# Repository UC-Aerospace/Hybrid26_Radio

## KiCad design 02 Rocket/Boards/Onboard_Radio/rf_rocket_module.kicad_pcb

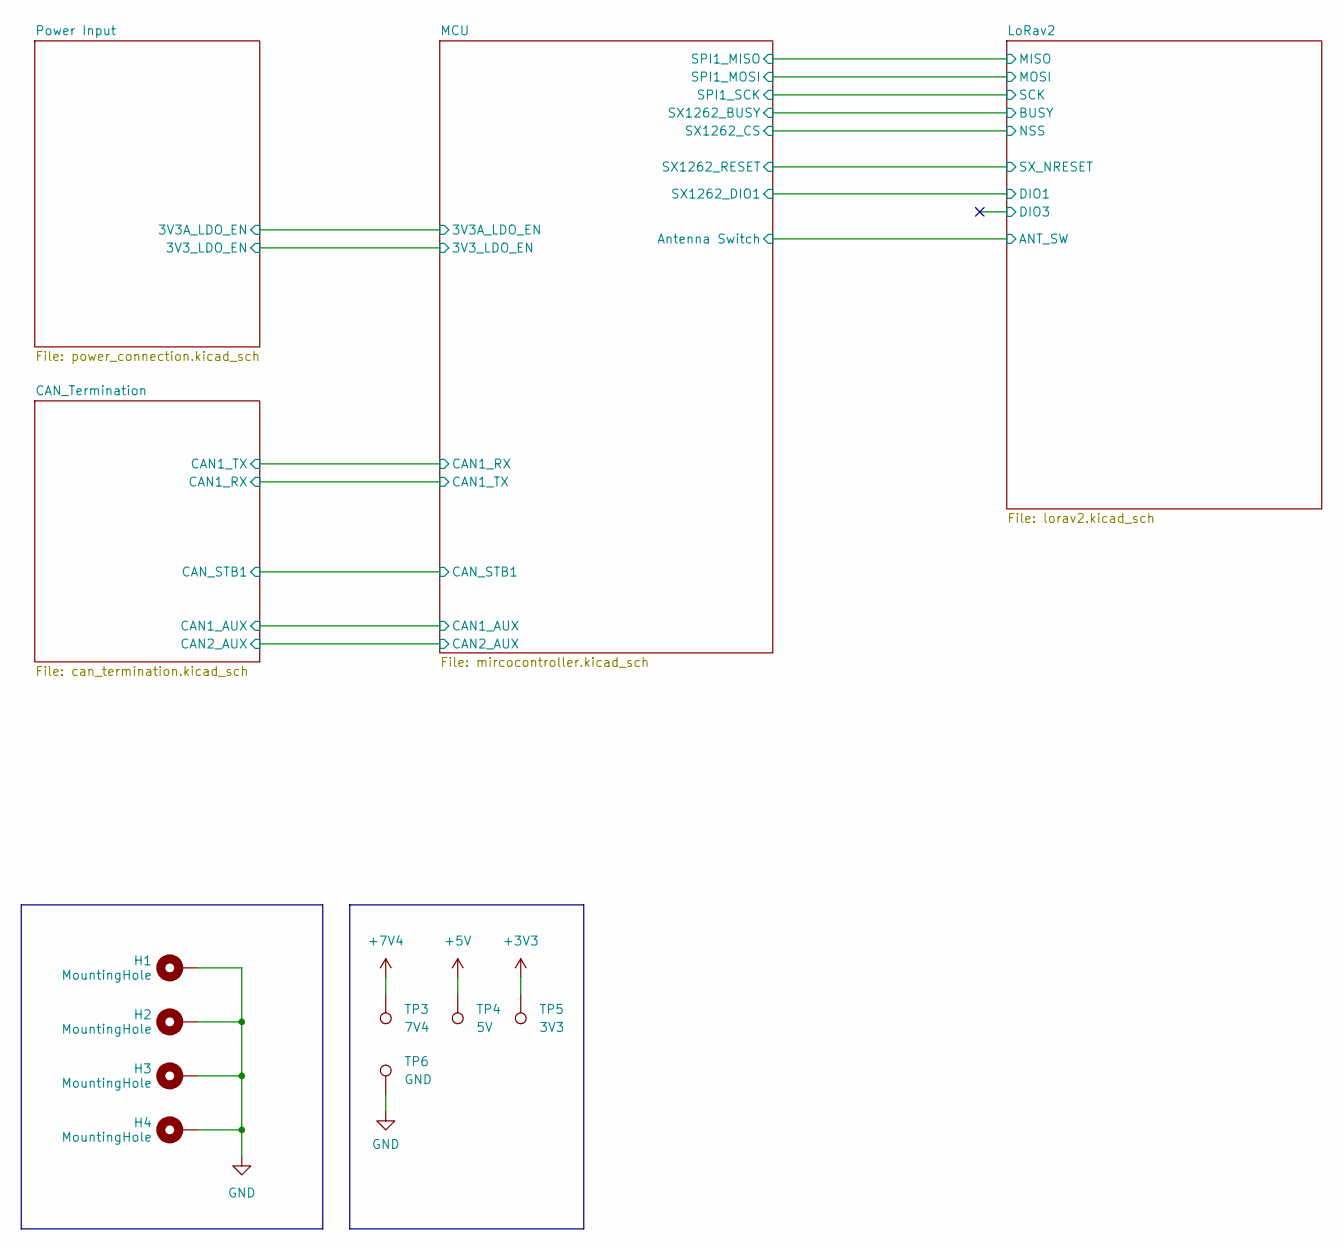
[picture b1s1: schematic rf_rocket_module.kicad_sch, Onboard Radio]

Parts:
H1, H2, H3, H4: MountingHole; MountingHole_3.2mm_M3_DIN965_Pad
TP3: 7V4; TestPoint_Pad_1.0x1.0mm
TP4: 5V; TestPoint_Pad_1.0x1.0mm
TP5: 3V3; TestPoint_Pad_1.0x1.0mm
TP6: GND; TestPoint_Pad_1.0x1.0mm

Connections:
GND: H1.1 (1_1), H2.1 (1_1), H3.1 (1_1), H4.1 (1_1), TP6.1; also elsewhere on the board

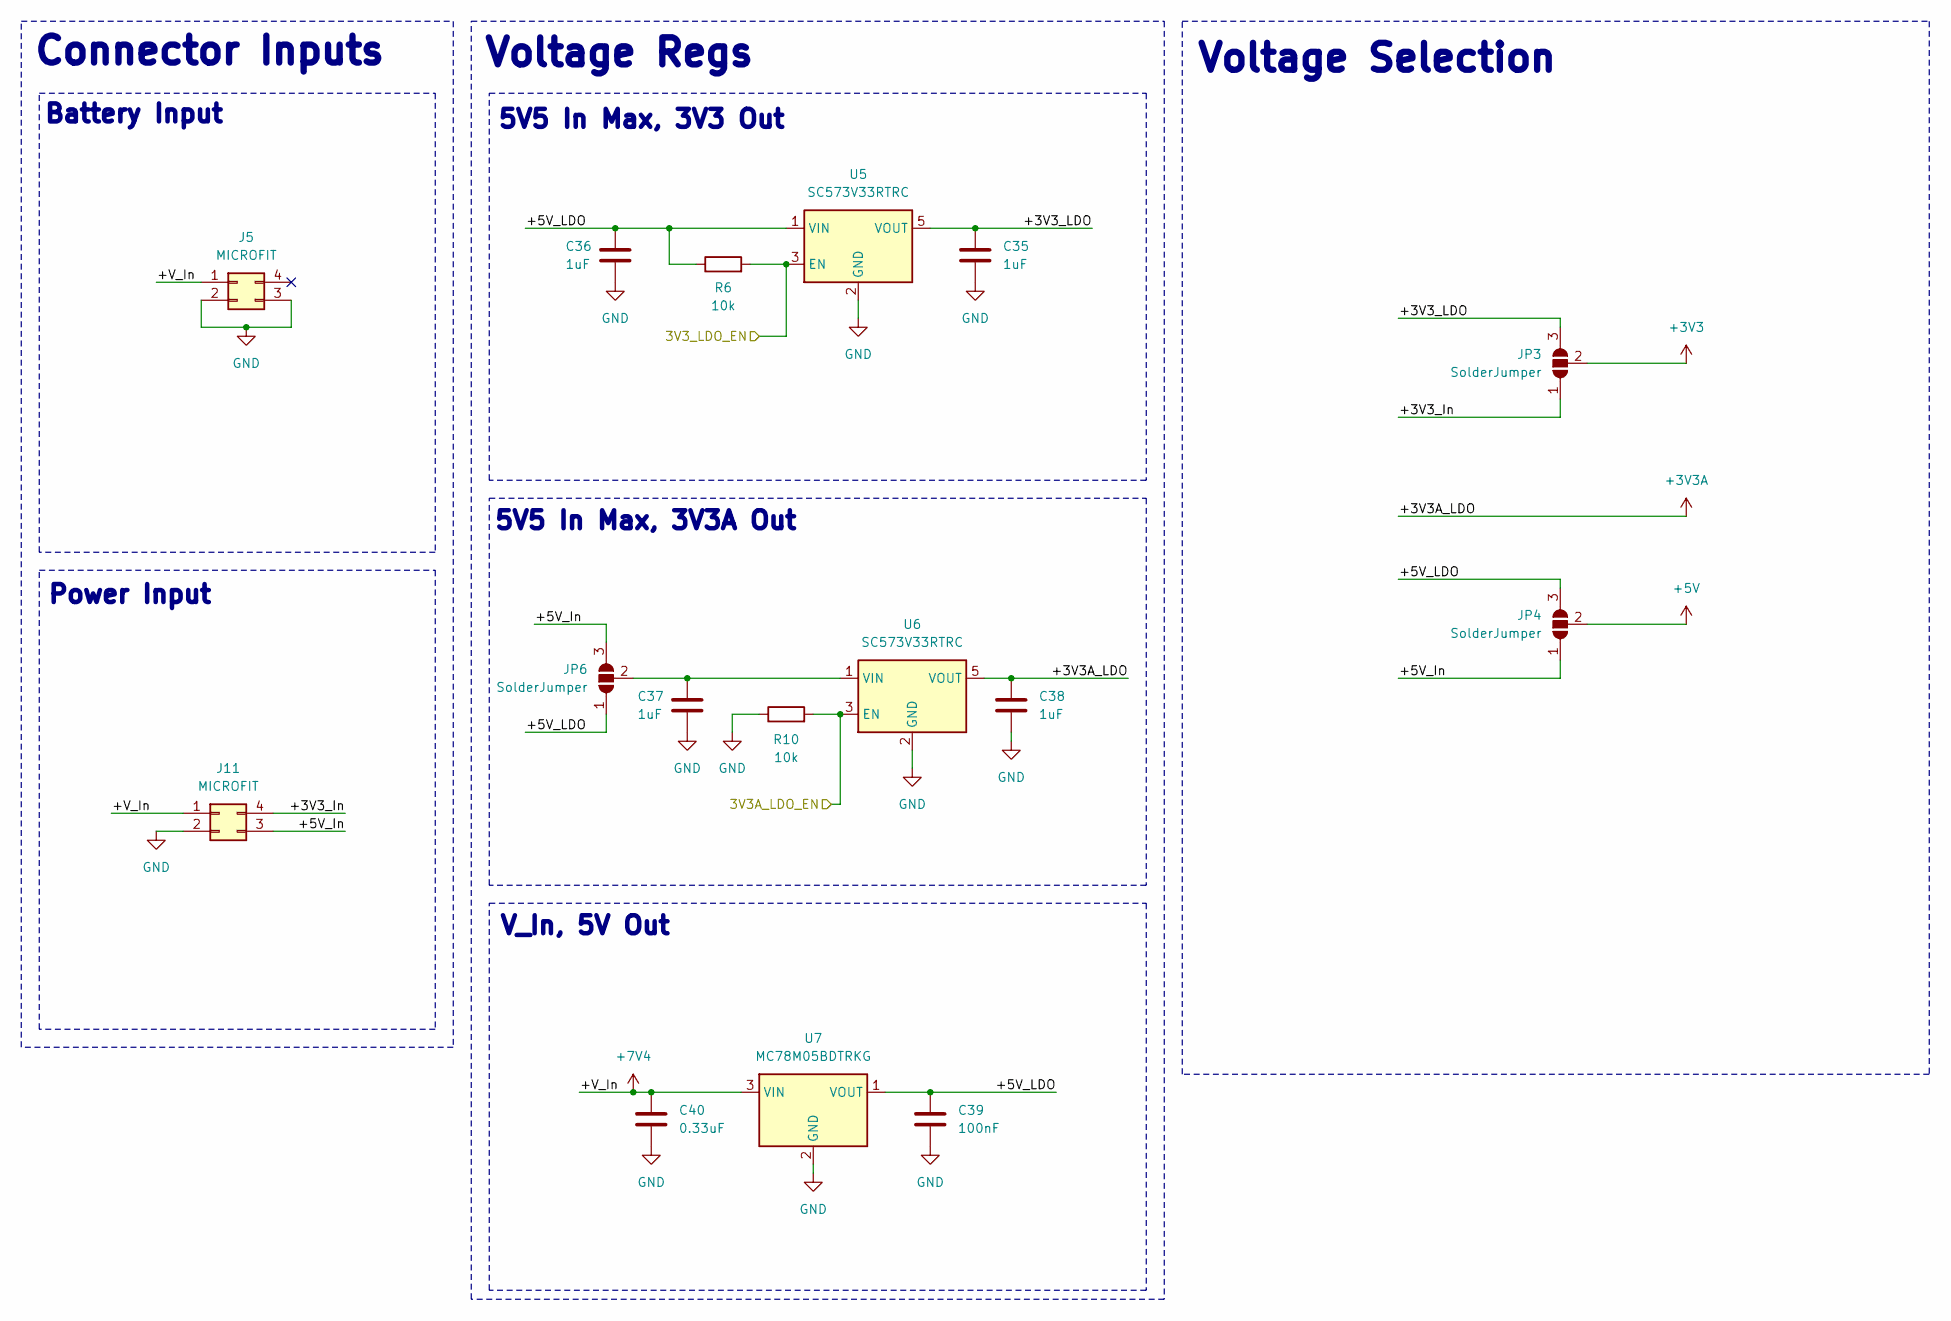
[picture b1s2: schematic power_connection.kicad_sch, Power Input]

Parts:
C35, C36, C37, C38: 1uF; C_0603_1608Metric; Voltage 10V; MPN GCM033C71A104KE02J; LCSC Part # C20041637
C39: 100nF; C_0603_1608Metric; Voltage 100V; MPN CL10E104KC8VPNC; LCSC Part # C16194197
C40: 0.33uF; C_0603_1608Metric; Voltage 50v; MPN CGA3E3X7R1H334K080AB; LCSC Part # C2178511
J5, J11: MICROFIT; Molex_Micro-Fit_3.0_43045-0412_2x02_P3.00mm_Vertical; MPN 0430450412; LCSC Part # C277721
JP3, JP4, JP6: SolderJumper; SolderJumper-3_P1.3mm_Open_RoundedPad1.0x1.5mm
R6, R10: 10k; R_0603_1608Metric; MPN RC0603FR-0710KL; LCSC Part # RC0603FR-0710KL
U5, U6: SC573V33RTRC; SOT-353_SC-70-5; MPN SC573V33RTRC; LCSC Part # C3751903
U7: MC78M05BDTRKG; TO-252-3_TabPin2; MPN MC78M05BDTRKG

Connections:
+3V3: JP3.2 (C); also elsewhere on the board
+3V3A: C38.1, U6.5 (VOUT); also elsewhere on the board
+5V: JP4.2 (C); also elsewhere on the board
+7V4: C40.1, J5.1, J11.1, U7.3 (VIN); also elsewhere on the board
/MCU/3V3A_LDO_EN: R10.2, U6.3 (EN); also elsewhere on the board
/MCU/3V3_LDO_EN: R6.2, U5.3 (EN); also elsewhere on the board
/Power Input/+3V3_In: J11.4, JP3.1 (A)
/Power Input/+3V3_LDO: C35.1, JP3.3 (B), U5.5 (VOUT)
/Power Input/+5V_In: J11.3, JP4.1 (A), JP6.3 (B)
/Power Input/+5V_LDO: C36.1, C39.1, JP4.3 (B), JP6.1 (A), R6.1, U5.1 (VIN), U7.1 (VOUT)
GND: C35.2, C36.2, C37.2, C38.2, C39.2, C40.2, J5.2, J5.3, J11.2, R10.1, U5.2 (GND), U6.2 (GND), U7.2 (GND); also elsewhere on the board
unnamed: C37.1, JP6.2 (C), U6.1 (VIN)

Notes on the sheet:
V_In, 5V Out
Voltage Regs
5V5 In Max, 3V3A Out
5V5 In Max, 3V3 Out
Voltage Selection
Connector Inputs
Power Input
Battery Input

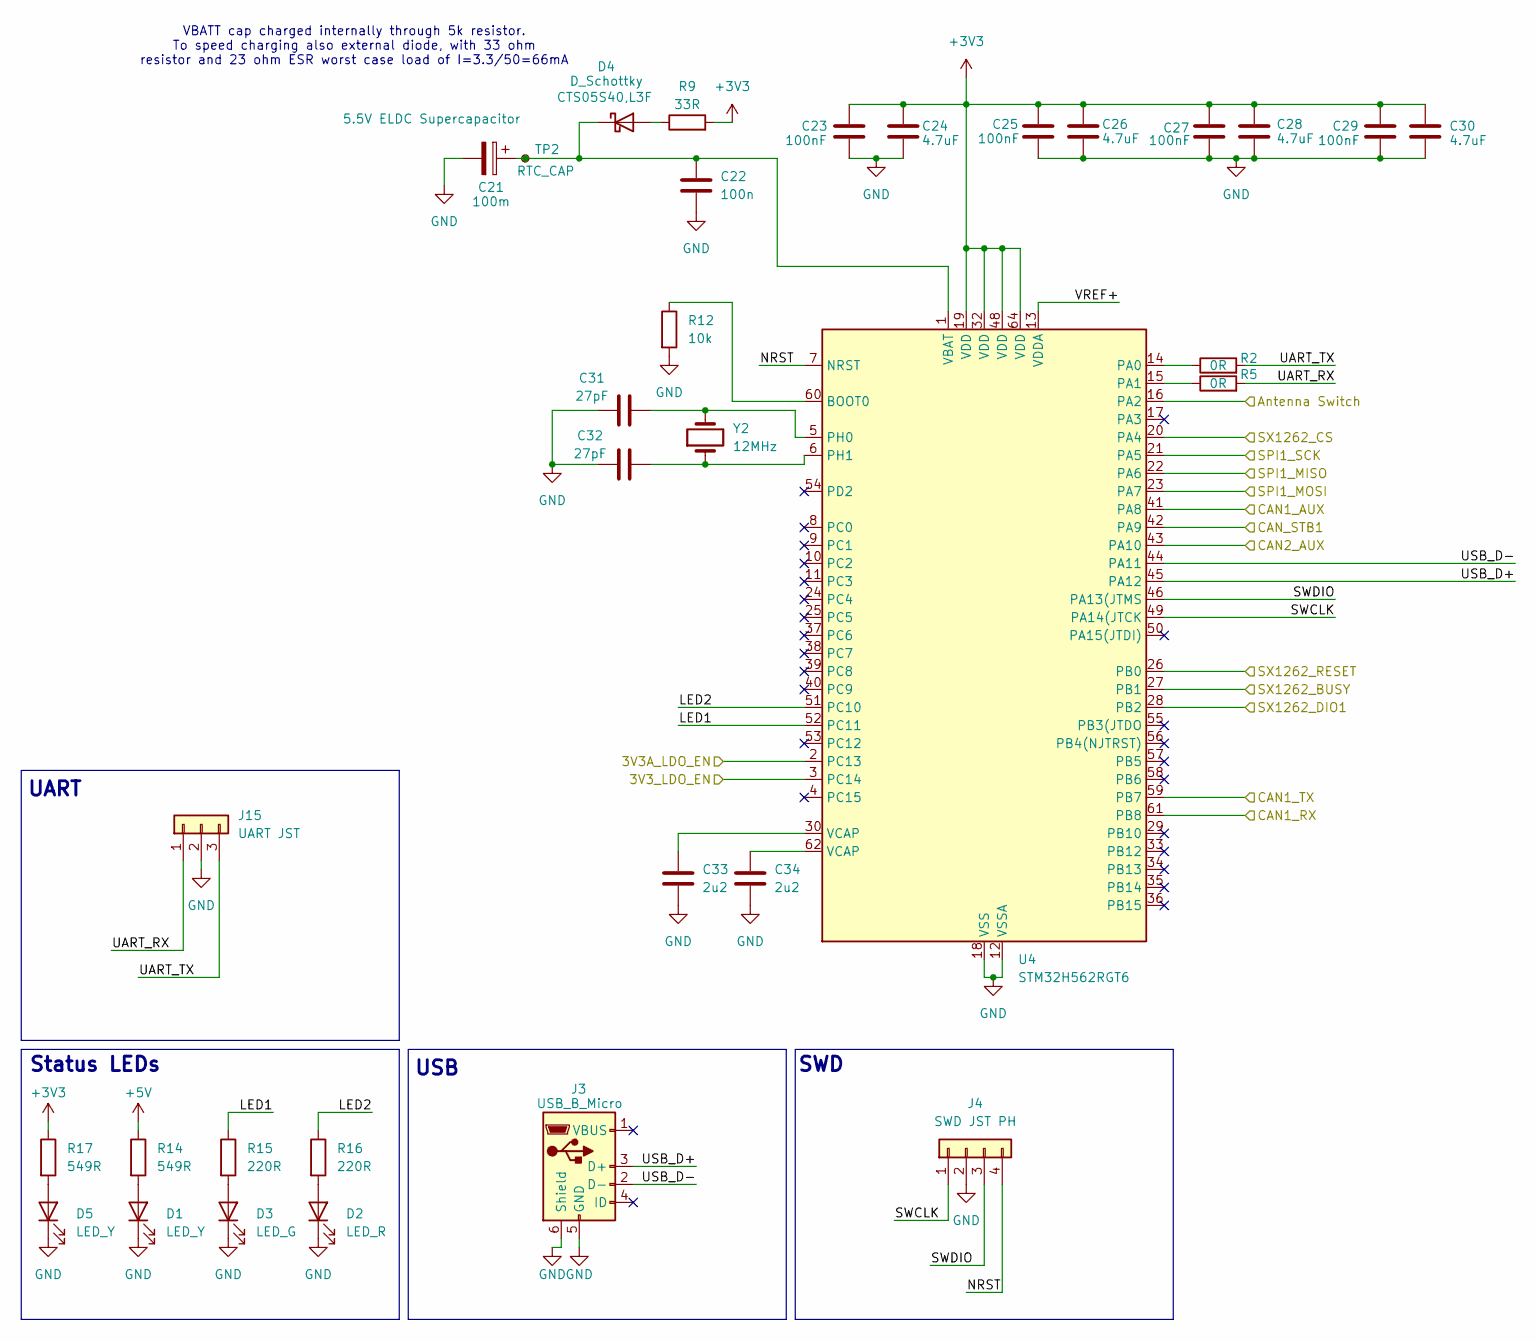
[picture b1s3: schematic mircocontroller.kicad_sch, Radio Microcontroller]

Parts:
C21: 100m; CP_Radial_D14.0mm_P5.00mm; MPN RSCBN1045R5G07014T
C22: 100n; C_0402_1005Metric; Voltage 50V; MPN KAM05FR71H104KH
C23, C25, C27, C29: 100nF; C_0603_1608Metric; Voltage 100V; MPN CL10E104KC8VPNC; LCSC Part # C16194197
C24, C26, C28, C30: 4.7uF; C_0603_1608Metric; Voltage 25V; MPN GRT188C81E475KE13D; LCSC Part # C907917
C31, C32: 27pF; C_0603_1608Metric; MPN GCM1885C2A270JA16D; LCSC Part # C909846
C33, C34: 2u2; R_0603_1608Metric; Voltage 25V; MPN GRM188R61E225KA12D; LCSC Part # C77047
D1, D5: LED_Y; LED_0603_1608Metric; MPN TLMY1100-GS15; LCSC Part # C20433848
D2: LED_R; LED_0603_1608Metric; MPN TLMS1000-GS15; LCSC Part # C23070302
D3: LED_G; LED_0603_1608Metric; MPN TLMG1100-GS15; LCSC Part # C20433785
D4: D_Schottky; D_SOD-882; MPN CTS05S40,L3F; LCSC Part # C396063
J3: USB_B_Micro; USB_Micro-B_Amphenol_10118193-0001LF_Horizontal; Voltage 100V; MPN 10118193-0001LF; LCSC Part # C132562
J4: SWD JST PH; JST_PH_B4B-PH-K_1x04_P2.00mm_Vertical; Voltage 100V; MPN B4B-PH-K-S; LCSC Part # C131334
J15: UART JST; JST_PH_B3B-PH-K_1x03_P2.00mm_Vertical; MPN B3B-PH-K-S
R2, R5: 0R; R_0402_1005Metric; MPN CRCW04020000Z0ED; LCSC Part # C190119
R9: 33R; R_0603_1608Metric; MPN RC0201FR-0733RL; LCSC Part # C295794
R12: 10k; R_0603_1608Metric; MPN RC0603FR-0710KL; LCSC Part # RC0603FR-0710KL
R14, R17: 549R; R_0603_1608Metric; MPN RMCF0603FT549R; LCSC Part # C4237517
R15, R16: 220R; R_0603_1608Metric; MPN RMCF0603JT220R; LCSC Part # C2484076
TP2: RTC_CAP; TestPoint_Pad_1.0x1.0mm
U4: STM32H562RGT6; LQFP-64_10x10mm_P0.5mm; MPN STM32H562RGT6; LCSC Part # C19711662
Y2: 12MHz; Crystal_SMD_Abracon_ABM8G-4Pin_3.2x2.5mm; MPN ABM8G-12.000MHZ-18-D2Y-T

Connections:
+3V3: C23.1, C24.1, C25.1, C26.1, C27.1, C28.1, C29.1, C30.1, R9.2, R17.1, U4.19 (VDD), U4.32 (VDD), U4.48 (VDD), U4.64 (VDD); also elsewhere on the board
+5V: R14.1; also elsewhere on the board
/CAN_Termination/CAN1_AUX: U4.41 (PA8); also elsewhere on the board
/CAN_Termination/CAN1_RX: U4.59 (PB7); also elsewhere on the board
/CAN_Termination/CAN1_TX: U4.61 (PB8); also elsewhere on the board
/CAN_Termination/CAN2_AUX: U4.43 (PA10); also elsewhere on the board
/CAN_Termination/CAN_STB1: U4.42 (PA9); also elsewhere on the board
/LoRav2/ANT_SW: U4.16 (PA2); also elsewhere on the board
/LoRav2/BUSY: U4.27 (PB1); also elsewhere on the board
/LoRav2/DIO1: U4.28 (PB2); also elsewhere on the board
/LoRav2/MISO: U4.22 (PA6); also elsewhere on the board
/LoRav2/MOSI: U4.23 (PA7); also elsewhere on the board
/LoRav2/NSS: U4.20 (PA4); also elsewhere on the board
/LoRav2/SCK: U4.21 (PA5); also elsewhere on the board
/LoRav2/SX_NRESET: U4.26 (PB0); also elsewhere on the board
/MCU/3V3A_LDO_EN: U4.2 (PC13); also elsewhere on the board
/MCU/3V3_LDO_EN: U4.3 (PC14); also elsewhere on the board
/MCU/LED1: R15.1, U4.52 (PC11)
/MCU/LED2: R16.1, U4.51 (PC10)
/MCU/NRST: J4.4, U4.7 (NRST)
/MCU/SWCLK: J4.1, U4.49 (PA14(JTCK)
/MCU/SWDIO: J4.3, U4.46 (PA13(JTMS)
/MCU/UART_RX: J15.1, R5.2
/MCU/UART_TX: J15.3, R2.2
/MCU/USB_D+: J3.3 (D+), U4.45 (PA12)
/MCU/USB_D-: J3.2 (D-), U4.44 (PA11)
/MCU/VREF+: U4.13 (VDDA)
GND: C21.2, C22.2, C23.2, C24.2, C25.2, C26.2, C27.2, C28.2, C29.2, C30.2, C31.1, C32.2, C33.2, C34.2, D1.1 (K), D2.1 (K), D3.1 (K), D5.1 (K), J3.5 (GND), J3.6 (Shield), J4.2, J15.2, R12.2, U4.12 (VSSA), U4.18 (VSS), U4.31 (VSS), U4.47 (VSS), U4.63 (VSS); also elsewhere on the board
unnamed: C33.1, U4.30 (VCAP)
unnamed: C34.1, U4.62 (VCAP)
unnamed: D1.2 (A), R14.2
unnamed: D2.2 (A), R16.2
unnamed: D3.2 (A), R15.2
unnamed: D4.2 (A), R9.1
unnamed: C21.1, C22.1, D4.1 (K), TP2.1, U4.1 (VBAT)
unnamed: D5.2 (A), R17.2
unnamed: R12.1, U4.60 (BOOT0)
unnamed: R2.1, U4.14 (PA0)
unnamed: R5.1, U4.15 (PA1)
unnamed: C31.2, U4.5 (PH0), Y2.3 (2)
unnamed: C32.1, U4.6 (PH1), Y2.1

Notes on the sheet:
VBATT cap charged internally through 5k resistor. To speed charging also external diode, with 33 ohm resistor and 23 ohm ESR worst case load of I=3.3/50=66mA
SWD
UART
USB
Status LEDs

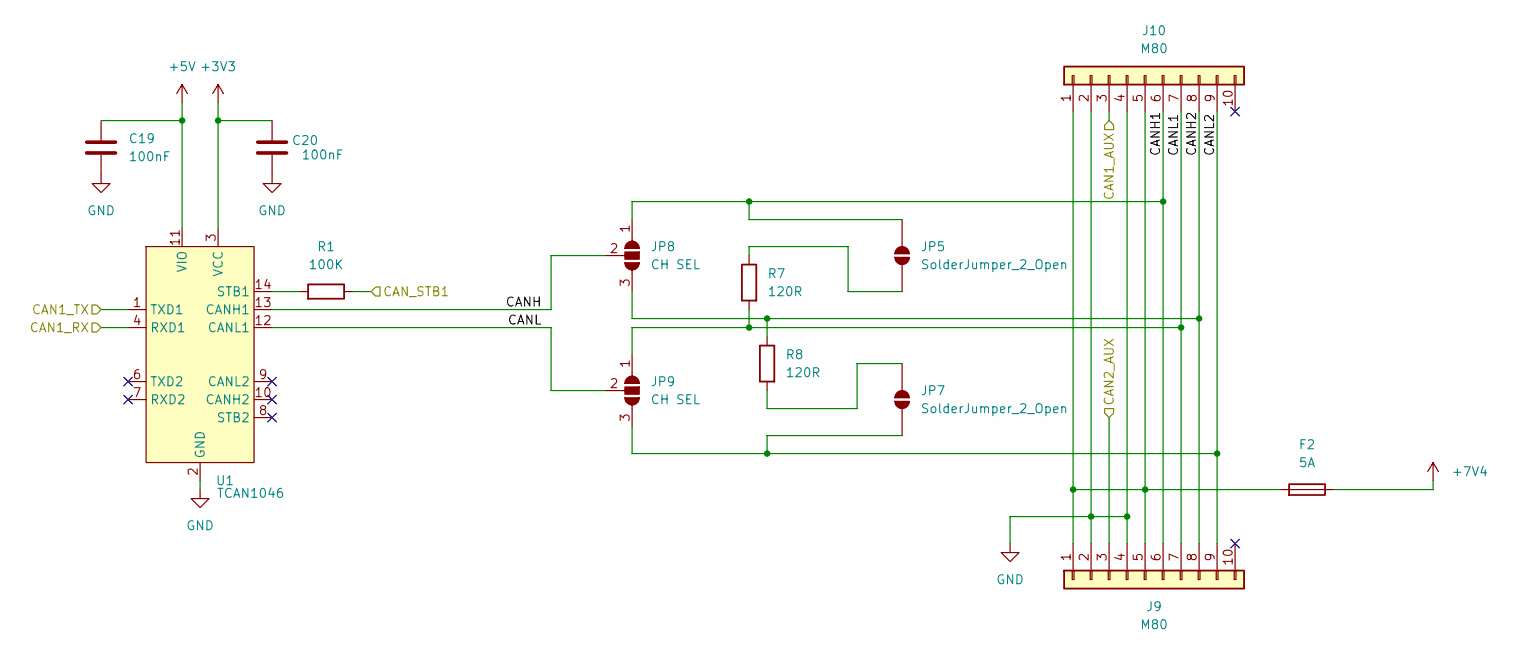
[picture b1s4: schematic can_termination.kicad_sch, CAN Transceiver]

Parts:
C19, C20: 100nF; C_0603_1608Metric; Voltage 100V; MPN CL10E104KC8VPNC; LCSC Part # C16194197
F2: 5A; Fuse_1206_3216Metric; Voltage 63V; MPN C1F 5; LCSC Part # C3166463
J9, J10: M80; HARWIN_M80-5011005; MPN M80-5301042; LCSC Part # C17382082
JP5, JP7: SolderJumper_2_Open; SolderJumper-2_P1.3mm_Open_RoundedPad1.0x1.5mm
JP8, JP9: CH SEL; SolderJumper-3_P1.3mm_Open_RoundedPad1.0x1.5mm
R1: 100K; R_0603_1608Metric; MPN RMCF0603FT100K; LCSC Part # C237792
R7, R8: 120R; R_0603_1608Metric; MPN RMCF0603JT120R; LCSC Part # C3995226
U1: TCAN1046; Texas_DYY0014A_TSOT-23-14; MPN TCAN1046AVDYYRQ1; LCSC Part # C3233845

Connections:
+3V3: C20.1, U1.3 (VCC); also elsewhere on the board
+5V: C19.1, U1.11 (VIO); also elsewhere on the board
+7V4: F2.1; also elsewhere on the board
/CAN_Termination/CAN1_AUX: J10.3; also elsewhere on the board
/CAN_Termination/CAN1_RX: U1.4 (RXD1); also elsewhere on the board
/CAN_Termination/CAN1_TX: U1.1 (TXD1); also elsewhere on the board
/CAN_Termination/CAN2_AUX: J9.3; also elsewhere on the board
/CAN_Termination/CANH: JP8.2 (C), U1.13 (CANH1)
/CAN_Termination/CANH1: J9.6, J10.6, JP5.2 (B), JP8.1 (A)
/CAN_Termination/CANH2: J9.8, J10.8, JP8.3 (B), R8.1
/CAN_Termination/CANL: JP9.2 (C), U1.12 (CANL1)
/CAN_Termination/CANL1: J9.7, J10.7, JP9.1 (A), R7.2
/CAN_Termination/CANL2: J9.9, J10.9, JP7.1 (A), JP9.3 (B)
/CAN_Termination/CAN_STB1: R1.1; also elsewhere on the board
GND: C19.2, C20.2, J9.2, J9.4, J10.2, J10.4, U1.2 (GND), U1.5 (GND); also elsewhere on the board
unnamed: F2.2, J9.1, J9.5, J10.1, J10.5
unnamed: JP5.1 (A), R7.1
unnamed: JP7.2 (B), R8.2
unnamed: R1.2, U1.14 (STB1)

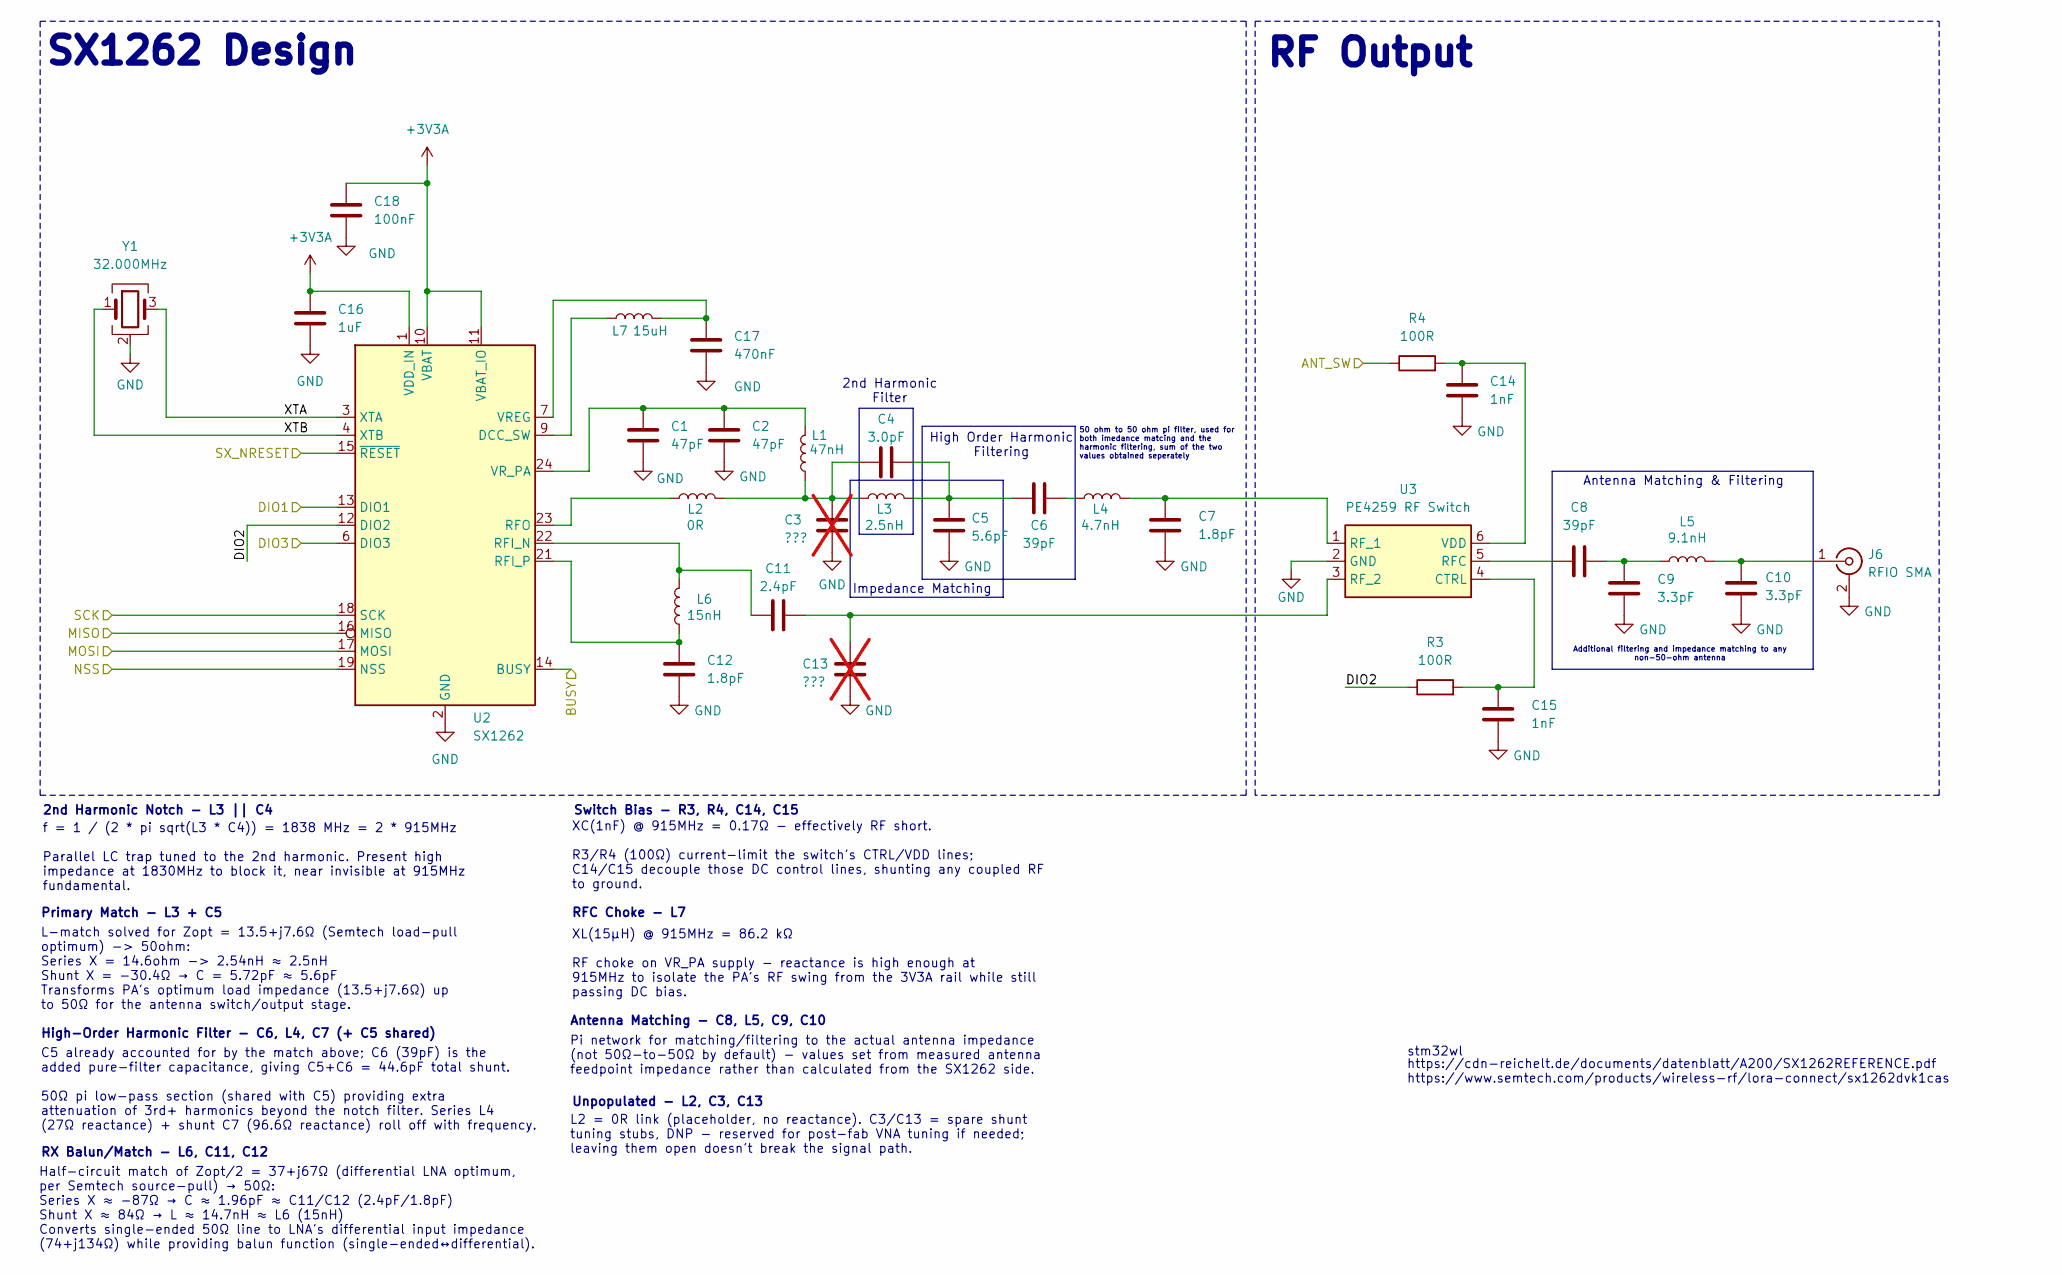
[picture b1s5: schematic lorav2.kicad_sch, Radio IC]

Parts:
C1, C2: 47pF; C_0402_1005Metric; Voltage 50V; MPN GJM1555C1H470JB01D; LCSC Part # C161322
C3, C13: ???; C_0402_1005Metric; not fitted
C4: 3.0pF; C_0402_1005Metric; Voltage 50V; MPN GJM1555C1H3R0BB01D; LCSC Part # C88891
C5: 5.6pF; C_0402_1005Metric; Voltage 50V; MPN GJM1555C1H5R6CB01D; LCSC Part # C88895
C6, C8: 39pF; C_0402_1005Metric; Voltage 50V; MPN GJM1555C1H390JB01D; LCSC Part # C426038
C7, C12: 1.8pF; C_0402_1005Metric; Voltage 50V; MPN GJM1555C1H1R8BB01D; LCSC Part # C76902
C9, C10: 3.3pF; C_0402_1005Metric; Voltage 50V; MPN GJM1555C1H3R3BB01D; LCSC Part # C76906
C11: 2.4pF; C_0402_1005Metric; Voltage 50V; MPN GJM1555C1H2R4BB01D; LCSC Part # C88888
C14, C15: 1nF; C_0402_1005Metric; Voltage 100V; MPN GRM155R72A102KA01D; LCSC Part # C162197
C16: 1uF; C_0402_1005Metric; Voltage 16V; MPN GRM155R61C105KA12D; LCSC Part # C77006
C17: 470nF; C_0402_1005Metric; Voltage 10V; MPN GRM155R71A474KE01D; LCSC Part # C88946
C18: 100nF; C_0402_1005Metric; Voltage 50V; MPN GRM155R71H104KE14D; LCSC Part # C77020
J6: RFIO SMA; SMA-KE-16.5A_EdgeMount; MPN 142-0701-841; LCSC Part # C3173357
L1: 47nH; L_0402_1005Metric; MPN LQW15AN47NJ00D; LCSC Part # C192855
L2: 0R; R_0402_1005Metric; MPN CRCW04020000Z0ED; LCSC Part # C190119
L3: 2.5nH; L_0402_1005Metric; MPN LQW15AN2N5C00D; LCSC Part # C703121
L4: 4.7nH; L_0402_1005Metric; MPN LQW15AN4N7C00D; LCSC Part # C167480
L5: 9.1nH; L_0402_1005Metric; MPN LQW15AN9N1H00D; LCSC Part # C337956
L6: 15nH; L_0402_1005Metric; MPN LQW15AN15NH00D; LCSC Part # C91621
L7: 15uH; L_0805_2012Metric; MPN MLZ2012M150WT000; LCSC Part # C383402
R3, R4: 100R; R_0402_1005Metric; MPN CRCW0402100RFKED; LCSC Part # C82865
U2: SX1262; QFN-24-1EP_4x4mm_P0.5mm_EP2.6x2.6mm; MPN SX1262IMLTRT; LCSC Part # C191341
U3: PE4259 RF Switch; SOT-363_SC-70-6; MPN 4259-63; LCSC Part # C470892
Y1: 32.000MHz; Oscillator_SMD_ECS_2520MV-xxx-xx-4Pin_2.5x2.0mm; MPN TYETBCSANF-32.000000

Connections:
+3V3A: C16.1, C18.1, U2.1 (VDD_IN), U2.10 (VBAT), U2.11 (VBAT_IO); also elsewhere on the board
/LoRav2/ANT_SW: R4.1; also elsewhere on the board
/LoRav2/BUSY: U2.14 (BUSY); also elsewhere on the board
/LoRav2/DIO1: U2.13 (DIO1); also elsewhere on the board
/LoRav2/DIO2: R3.1, U2.12 (DIO2)
/LoRav2/DIO3: U2.6 (DIO3)
/LoRav2/MISO: U2.16 (MISO); also elsewhere on the board
/LoRav2/MOSI: U2.17 (MOSI); also elsewhere on the board
/LoRav2/NSS: U2.19 (NSS); also elsewhere on the board
/LoRav2/SCK: U2.18 (SCK); also elsewhere on the board
/LoRav2/SX_NRESET: U2.15 (~RESET); also elsewhere on the board
/LoRav2/XTA: U2.3 (XTA), Y1.3
/LoRav2/XTB: U2.4 (XTB), Y1.1
GND: C1.2, C2.2, C3.2, C5.2, C7.2, C9.2, C10.2, C12.2, C13.2, C14.2, C15.2, C16.2, C17.2, C18.2, J6.2 (Ext), U2.2 (GND), U2.5 (GND), U2.8 (GND), U2.20 (GND), U2.25 (GND), U3.2 (GND), Y1.2 (G), Y1.4 (G); also elsewhere on the board
unnamed: C3.1, C4.1, L1.1, L2.2, L3.1
unnamed: C4.2, C5.1, C6.1, L3.2
unnamed: C6.2, L4.1
unnamed: C8.2, C9.1, L5.1
unnamed: C10.1, J6.1 (In), L5.2
unnamed: L7.1, U2.9 (DCC_SW)
unnamed: C11.1, L6.2, U2.22 (RFI_N)
unnamed: C12.1, L6.1, U2.21 (RFI_P)
unnamed: L2.1, U2.23 (RFO)
unnamed: C17.1, L7.2, U2.7 (VREG)
unnamed: C1.1, C2.1, L1.2, U2.24 (VR_PA)
unnamed: C15.1, R3.2, U3.4 (CTRL)
unnamed: C8.1, U3.5 (RFC)
unnamed: C7.1, L4.2, U3.1 (RF_1)
unnamed: C11.2, C13.1, U3.3 (RF_2)
unnamed: C14.1, R4.2, U3.6 (VDD)

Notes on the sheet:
Additional filtering and impedance matching to any non-50-ohm antenna
C5 already accounted for by the match above; C6 (39pF) is the added pure-filter capacitance, giving C5+C6 = 44.6pF total shunt. 50Ω pi low-pass section (shared with C5) providing extra attenuation of 3rd+ harmonics beyond the notch filter. Series L4 (27Ω reactance) + shunt C7 (96.6Ω reactance) roll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
https://cdn-reichelt.de/documents/datenblatt/A200/SX1262REFERENCE.pdf https://www.semtech.com/products/wireless-rf/lora-connect/sx1262dvk1cas
Impedance Matching
Primary Match - L3 + C5
Pi network for matching/filtering to the actual antenna impedance (not 50Ω-to-50Ω by default) - values set from measured antenna feedpoint impedance rather than calculated from the SX1262 side.
High-Order Harmonic Filter - C6, L4, C7 (+ C5 shared)
RX Balun/Match - L6, C11, C12
L-match solved for Zopt = 13.5+j7.6Ω (Semtech load-pull optimum) -> 50ohm: Series X = 14.6ohm -> 2.54nH ≈ 2.5nH Shunt X = -30.4Ω → C = 5.72pF ≈ 5.6pF Transforms PA's optimum load impedance (13.5+j7.6Ω) up to 50Ω for the antenna switch/output stage.
Half-circuit match of Zopt/2 = 37+j67Ω (differential LNA optimum, per Semtech source-pull) → 50Ω: Series X ≈ −87Ω → C ≈ 1.96pF ≈ C11/C12 (2.4pF/1.8pF) Shunt X ≈ 84Ω → L ≈ 14.7nH ≈ L6 (15nH) Converts single-ended 50Ω line to LNA's differential input impedance (74+j134Ω) while providing balun functio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
Antenna Matching - C8, L5, C9, C10
Unpopulated - L2, C3, C13
RFC Choke - L7
2nd Harmonic Notch - L3 || C4
f = 1 / (2 * pi sqrt(L3 * C4)) = 1838 MHz = 2 * 915MHz Parallel LC trap tuned to the 2nd harmonic. Present high impedance at 1830MHz to block it, near invisible at 915MHz fundamental.
stm32wl
Antenna Matching & Filtering
High Order Harmonic Filtering
SX1262 Design
RF Output
50 ohm to 50 ohm pi filter, used for both imedance matcing and the harmonic filtering, sum of the two values obtained seperately
2nd Harmonic Filter
XL(15µH) @ 915MHz = 86.2 kΩ RF choke on VR_PA supply - reactance is high enough at 915MHz to isolate the PA's RF swing from the 3V3A rail while still passing DC bias.
Switch Bias - R3, R4, C14, C15
XC(1nF) @ 915MHz = 0.17Ω - effectively RF short. R3/R4 (100Ω) current-limit the switch's CTRL/VDD lines; C14/C15 decouple those DC control lines, shunting any coupled RF to ground.
L2 = 0R link (placeholder, no reactance). C3/C13 = spare shunt tuning stubs, DNP - reserved for post-fab VNA tuning if needed; leaving them open doesn't break the signal path.

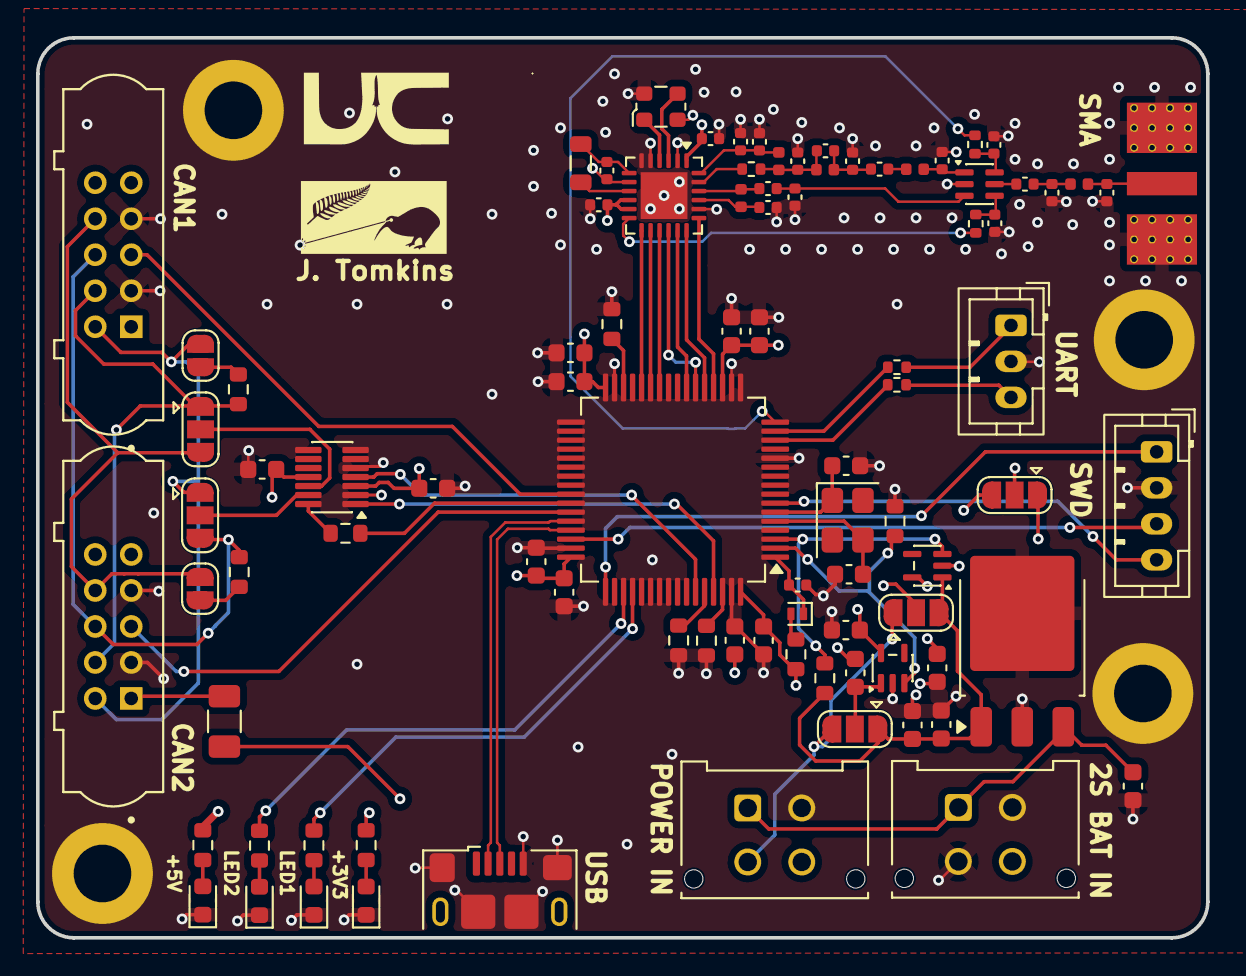
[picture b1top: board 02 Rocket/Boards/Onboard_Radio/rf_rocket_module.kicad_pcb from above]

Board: 4 copper layers, 65.0 x 50.0 mm, 95 parts (0 on the bottom side), 76 nets.

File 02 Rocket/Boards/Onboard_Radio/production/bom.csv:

Designator,Footprint,Quantity,Value,LCSC Part #
"C1, C2",0402,2,47pF,C161322
"C10, C9",0402,2,3.3pF,C76906
C11,0402,1,2.4pF,C88888
"C12, C7",0402,2,1.8pF,C76902
"C14, C15",0402,2,1nF,C162197
C16,0402,1,1uF,C77006
C17,0402,1,470nF,C88946
C18,0402,1,100nF,C77020
"C19, C20, C23, C25, C27, C29, C39",0603,7,100nF,C16194197
C22,0402,1,100n,KAM05FR71H104KH
"C24, C26, C28, C30",0603,4,4.7uF,C907917
"C31, C32",0603,2,27pF,C909846
"C33, C34",0603,2,2u2,C77047
"C35, C36, C37, C38",0603,4,1uF,C20041637
C4,0402,1,3.0pF,C88891
C40,0603,1,0.33uF,C2178511
C5,0402,1,5.6pF,C88895
"C6, C8",0402,2,39pF,C426038
"D1, D5",0603,2,LED_Y,C20433848
D2,0603,1,LED_R,C23070302
D3,0603,1,LED_G,C20433785
D4,D_SOD-882,1,D_Schottky,C396063
F2,1206,1,5A,C3166463
"J10, J9",HARWIN_M80-5011005,2,M80,C17382082
"J11, J5",Molex_Micro-Fit_3.0_43045-0412_2x02_P3.00mm_Vertical,2,MICROFIT,C277721
J15,JST_PH_B3B-PH-K_1x03_P2.00mm_Vertical,1,UART JST,B3B-PH-K-S
J3,USB_Micro-B_Amphenol_10118193-0001LF_Horizontal,1,USB_B_Micro,C132562
J4,JST_PH_B4B-PH-K_1x04_P2.00mm_Vertical,1,SWD JST PH,C131334
J6,SMA-KE-16.5A_EdgeMount,1,RFIO SMA,C3173357
L1,0402,1,47nH,C192855
L2,0402,1,0R,C190119
L3,0402,1,2.5nH,C703121
L4,0402,1,4.7nH,C167480
L5,0402,1,9.1nH,C337956
L6,0402,1,15nH,C91621
L7,0805,1,15uH,C383402
R1,0603,1,100K,C237792
"R10, R6",0603,2,10k,
R12,0603,1,10k,C98220
"R14, R17",0603,2,549R,C4237517
"R15, R16",0603,2,220R,C2484076
"R2, R5",0402,2,0R,
"R3, R4",0402,2,100R,C82865
"R7, R8",0603,2,120R,C3995226
R9,0603,1,33R,C295794
U1,Texas_DYY0014A_TSOT-23-14,1,TCAN1046,C3233845
U2,QFN-24-1EP_4x4mm_P0.5mm_EP2.6x2.6mm,1,SX1262,C191341
U3,SOT-363_SC-70-6,1,PE4259 RF Switch,C470892
U4,LQFP-64_10x10mm_P0.5mm,1,STM32H562RGT6,C19711662
"U5, U6",SOT-353_SC-70-5,2,SC573V33RTRC,C3751903
U7,TO-252-3_TabPin2,1,MC78M05BDTRKG,MC78M05BDTRKG
Y1,Oscillator_SMD_ECS_2520MV-xxx-xx-4Pin_2.5x2.0mm,1,32.000MHz,TYETBCSANF-32.000000
Y2,Crystal_SMD_Abracon_ABM8G-4Pin_3.2x2.5mm,1,12MHz,ABM8G-12.000MHZ-18-D2Y-T
